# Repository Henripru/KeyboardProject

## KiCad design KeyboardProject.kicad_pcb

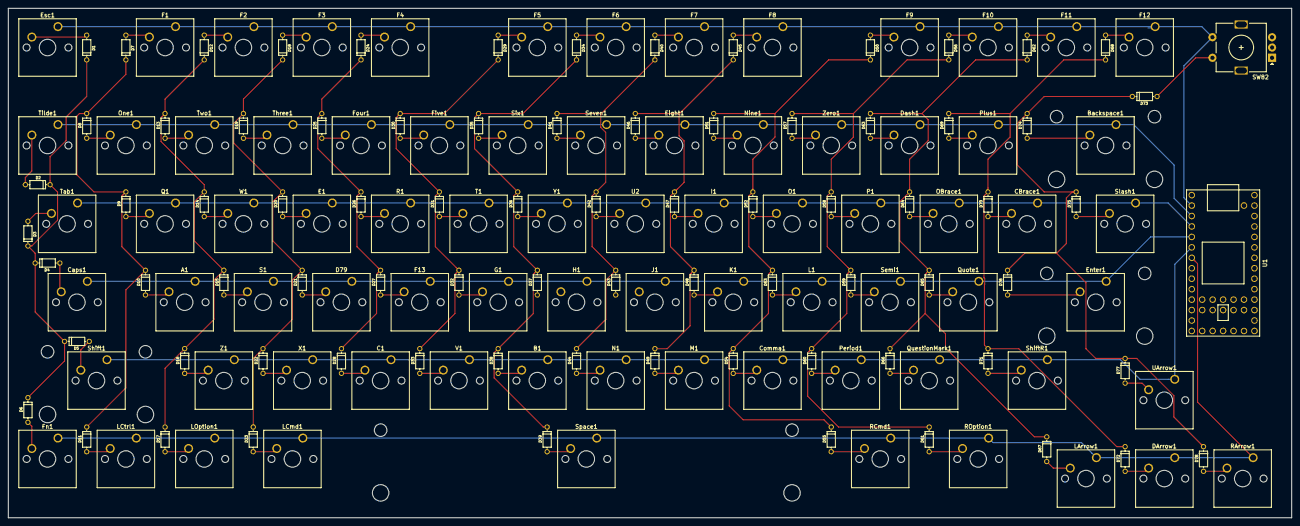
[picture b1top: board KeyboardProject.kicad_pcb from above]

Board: 2 copper layers, 311.9 x 123.8 mm, 157 parts (0 on the bottom side), 101 nets.

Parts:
A1: SW_Push; SW_Cherry_MX_1.00u_PCB
B1: SW_Push; SW_Cherry_MX_1.00u_PCB
Backspace1: SW_Push; SW_Cherry_MX_2.00u_PCB
C1: SW_Push; SW_Cherry_MX_1.00u_PCB
CBrace1: SW_Push; SW_Cherry_MX_1.00u_PCB
Caps1: SW_Push; SW_Cherry_MX_1.75u_PCB
Comma1: SW_Push; SW_Cherry_MX_1.00u_PCB
D1, D2, D3, D4, D5, D6, D7, D8, D9, D10, D11, D12, D13, D14, D15, D16, D17, D18, D19, D20, D21, D22, D23, D24, D25, D26, D27, D28, D29, D30, D31, D32, D33, D34, D35, D36, D37, D38, D39, D40, D41, D42, D43, D44, D45, D46, D47, D48, D49, D50, D51, D52, D53, D54, D55, D56, D57, D58, D59, D60, D61, D62, D63, D64, D65, D66, D67, D68, D69, D70, D71, D72, D73, D74, D75, D76, D77, D78: 1N4148W; DO-35
D79: SW_Push; SW_Cherry_MX_1.00u_PCB
DArrow1: SW_Push; SW_Cherry_MX_1.00u_PCB
Dash1: SW_Push; SW_Cherry_MX_1.00u_PCB
E1: SW_Push; SW_Cherry_MX_1.00u_PCB
Eight1: SW_Push; SW_Cherry_MX_1.00u_PCB
Enter1: SW_Push; SW_Cherry_MX_2.25u_PCB
Esc1: SW_Push; SW_Cherry_MX_1.00u_PCB
F1, F2, F3, F4, F5, F6, F7, F8, F9, F10, F11, F12, F13: SW_Push; SW_Cherry_MX_1.00u_PCB
Five1: SW_Push; SW_Cherry_MX_1.00u_PCB
Fn1: SW_Push; SW_Cherry_MX_1.00u_PCB
Four1: SW_Push; SW_Cherry_MX_1.00u_PCB
G1: SW_Push; SW_Cherry_MX_1.00u_PCB
H1: SW_Push; SW_Cherry_MX_1.00u_PCB
I1: SW_Push; SW_Cherry_MX_1.00u_PCB
J1: SW_Push; SW_Cherry_MX_1.00u_PCB
K1: SW_Push; SW_Cherry_MX_1.00u_PCB
L1: SW_Push; SW_Cherry_MX_1.00u_PCB
LArrow1: SW_Push; SW_Cherry_MX_1.00u_PCB
LCmd1: SW_Push; SW_Cherry_MX_1.25u_PCB
LCtrl1: SW_Push; SW_Cherry_MX_1.00u_PCB
LOption1: SW_Push; SW_Cherry_MX_1.00u_PCB
M1: SW_Push; SW_Cherry_MX_1.00u_PCB
N1: SW_Push; SW_Cherry_MX_1.00u_PCB
Nine1: SW_Push; SW_Cherry_MX_1.00u_PCB
O1: SW_Push; SW_Cherry_MX_1.00u_PCB
OBrace1: SW_Push; SW_Cherry_MX_1.00u_PCB
One1: SW_Push; SW_Cherry_MX_1.00u_PCB
P1: SW_Push; SW_Cherry_MX_1.00u_PCB
Period1: SW_Push; SW_Cherry_MX_1.00u_PCB
Plus1: SW_Push; SW_Cherry_MX_1.00u_PCB
Q1: SW_Push; SW_Cherry_MX_1.00u_PCB
QuestionMark1: SW_Push; SW_Cherry_MX_1.00u_PCB
Quote1: SW_Push; SW_Cherry_MX_1.00u_PCB
R1: SW_Push; SW_Cherry_MX_1.00u_PCB
RArrow1: SW_Push; SW_Cherry_MX_1.00u_PCB
RCmd1: SW_Push; SW_Cherry_MX_1.25u_PCB
ROption1: SW_Push; SW_Cherry_MX_1.25u_PCB
S1: SW_Push; SW_Cherry_MX_1.00u_PCB
SW82: Rotary_Encoder_Switch; RotaryEncoder_Alps_EC11E-Switch_Vertical_H20mm
Semi1: SW_Push; SW_Cherry_MX_1.00u_PCB
Seven1: SW_Push; SW_Cherry_MX_1.00u_PCB
Shift1: SW_Push; SW_Cherry_MX_2.00u_PCB
ShiftR1: SW_Push; SW_Cherry_MX_1.75u_PCB
Six1: SW_Push; SW_Cherry_MX_1.00u_PCB
Slash1: SW_Push; SW_Cherry_MX_1.50u_PCB
Space1: SW_Push; SW_Cherry_MX_6.25u_PCB
T1: SW_Push; SW_Cherry_MX_1.00u_PCB
Tab1: SW_Push; SW_Cherry_MX_1.50u_PCB
Three1: SW_Push; SW_Cherry_MX_1.00u_PCB
Tilde1: SW_Push; SW_Cherry_MX_1.00u_PCB
Two1: SW_Push; SW_Cherry_MX_1.00u_PCB
U1: Teensy4.0; Teensy40
U2: SW_Push; SW_Cherry_MX_1.00u_PCB
UArrow1: SW_Push; SW_Cherry_MX_1.00u_PCB
V1: SW_Push; SW_Cherry_MX_1.00u_PCB
W1: SW_Push; SW_Cherry_MX_1.00u_PCB
X1: SW_Push; SW_Cherry_MX_1.00u_PCB
Y1: SW_Push; SW_Cherry_MX_1.00u_PCB
Z1: SW_Push; SW_Cherry_MX_1.00u_PCB
Zero1: SW_Push; SW_Cherry_MX_1.00u_PCB

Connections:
/C0: D1.1, D2.1, D3.1, D4.1, D5.1, D6.1, U1.8
/C1: D7.1, D8.1, D9.1, D10.1, D11.1, U1.9
/C2: D12.1, D13.1, D14.1, D15.1, D16.1, D17.1, U1.10
/C3: D18.1, D19.1, D20.1, D21.1, D22.1, D23.1, U1.11
/C4: D24.1, D25.1, D26.1, D27.1, D28.1, U1.12
/C5: D29.1, D30.1, D31.1, D32.1, D33.1, U1.13
/C6: D34.1, D35.1, D36.1, D37.1, D38.1, D39.1, U1.14
/C7: D40.1, D41.1, D42.1, D43.1, D44.1, U1.27
/C8: D45.1, D46.1, D47.1, D48.1, D49.1, U1.21
/C9: D50.1, D51.1, D52.1, D53.1, D54.1, D55.1, U1.22
/C10: D56.1, D57.1, D58.1, D59.1, D60.1, D61.1, U1.23
/C11: D62.1, D63.1, D64.1, D65.1, D66.1, D67.1, U1.24
/C12: D68.1, D69.1, D70.1, D71.1, D72.1, U1.25
/C13: D73.1, D74.1, D75.1, D76.1, D77.1, D78.1, U1.26
/GND: SW82.C, U1.32
/R0: Esc1.1, F1.1, F2.1, F3.1, F4.1, F5.1, F6.1, F7.1, F8.1, F9.1, F10.1, F11.1, F12.1, SW82.S1, U1.2
/R1: Backspace1.1, Dash1.1, Eight1.1, Five1.1, Four1.1, Nine1.1, One1.1, Plus1.1, Seven1.1, Six1.1, Three1.1, Tilde1.1, Two1.1, U1.3, Zero1.1
/R2: CBrace1.1, E1.1, I1.1, O1.1, OBrace1.1, P1.1, Q1.1, R1.1, Slash1.1, T1.1, Tab1.1, U1.4, U2.1, W1.1, Y1.1
/R3: A1.1, Caps1.1, D79.1, Enter1.1, F13.1, G1.1, H1.1, J1.1, K1.1, L1.1, Quote1.1, S1.1, Semi1.1, U1.5
/R4: B1.1, C1.1, Comma1.1, M1.1, N1.1, Period1.1, QuestionMark1.1, Shift1.1, ShiftR1.1, U1.6, UArrow1.1, V1.1, X1.1, Z1.1
/R5: DArrow1.1, Fn1.1, LArrow1.1, LCmd1.1, LCtrl1.1, LOption1.1, RArrow1.1, RCmd1.1, ROption1.1, Space1.1, U1.7
/RotaryA: SW82.A, U1.29
/RotaryB: SW82.B, U1.30
/RotarySwitchOut: D73.2, SW82.S2
unnamed: A1.2, D10.2
unnamed: B1.2, D38.2
unnamed: Backspace1.2, D74.2
unnamed: C1.2, D28.2
unnamed: CBrace1.2, D70.2
unnamed: Caps1.2, D4.2
unnamed: Comma1.2, D54.2
unnamed: D1.2, Esc1.2
unnamed: D2.2, Tilde1.2
unnamed: D3.2, Tab1.2
unnamed: D5.2, Shift1.2
unnamed: D6.2, Fn1.2
unnamed: D7.2, F1.2
unnamed: D8.2, One1.2
unnamed: D9.2, Q1.2
unnamed: D11.2, LCtrl1.2
unnamed: D12.2, F2.2
unnamed: D13.2, Two1.2
unnamed: D14.2, W1.2
unnamed: D15.2, S1.2
unnamed: D16.2, Z1.2
unnamed: D17.2, LOption1.2
unnamed: D18.2, F3.2
unnamed: D19.2, Three1.2
unnamed: D20.2, E1.2
unnamed: D21.2, D79.2
unnamed: D22.2, X1.2
unnamed: D23.2, LCmd1.2
unnamed: D24.2, F4.2
unnamed: D25.2, Four1.2
unnamed: D26.2, R1.2
unnamed: D27.2, F13.2
unnamed: D29.2, F5.2
unnamed: D30.2, Five1.2
unnamed: D31.2, T1.2
unnamed: D32.2, G1.2
unnamed: D33.2, V1.2
unnamed: D34.2, F6.2
unnamed: D35.2, Six1.2
unnamed: D36.2, Y1.2
unnamed: D37.2, H1.2
unnamed: D39.2, Space1.2
unnamed: D40.2, F7.2
unnamed: D41.2, Seven1.2
unnamed: D42.2, U2.2
unnamed: D43.2, J1.2
unnamed: D44.2, N1.2
unnamed: D45.2, F8.2
unnamed: D46.2, Eight1.2
unnamed: D47.2, I1.2
unnamed: D48.2, K1.2
unnamed: D49.2, M1.2
unnamed: D50.2, F9.2
unnamed: D51.2, Nine1.2
unnamed: D52.2, O1.2
unnamed: D53.2, L1.2
unnamed: D55.2, RCmd1.2
unnamed: D56.2, F10.2
unnamed: D57.2, Zero1.2
unnamed: D58.2, P1.2
unnamed: D59.2, Semi1.2
unnamed: D60.2, Period1.2
unnamed: D61.2, ROption1.2
unnamed: D62.2, F11.2
unnamed: D63.2, Dash1.2
unnamed: D64.2, OBrace1.2
unnamed: D65.2, Quote1.2
unnamed: D66.2, QuestionMark1.2
unnamed: D67.2, LArrow1.2
unnamed: D68.2, F12.2
unnamed: D69.2, Plus1.2
unnamed: D71.2, ShiftR1.2
unnamed: D72.2, DArrow1.2
unnamed: D75.2, Slash1.2
unnamed: D76.2, Enter1.2
unnamed: D77.2, UArrow1.2
unnamed: D78.2, RArrow1.2

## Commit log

2020-01-03 upload first materials
2020-09-25 Save progress
